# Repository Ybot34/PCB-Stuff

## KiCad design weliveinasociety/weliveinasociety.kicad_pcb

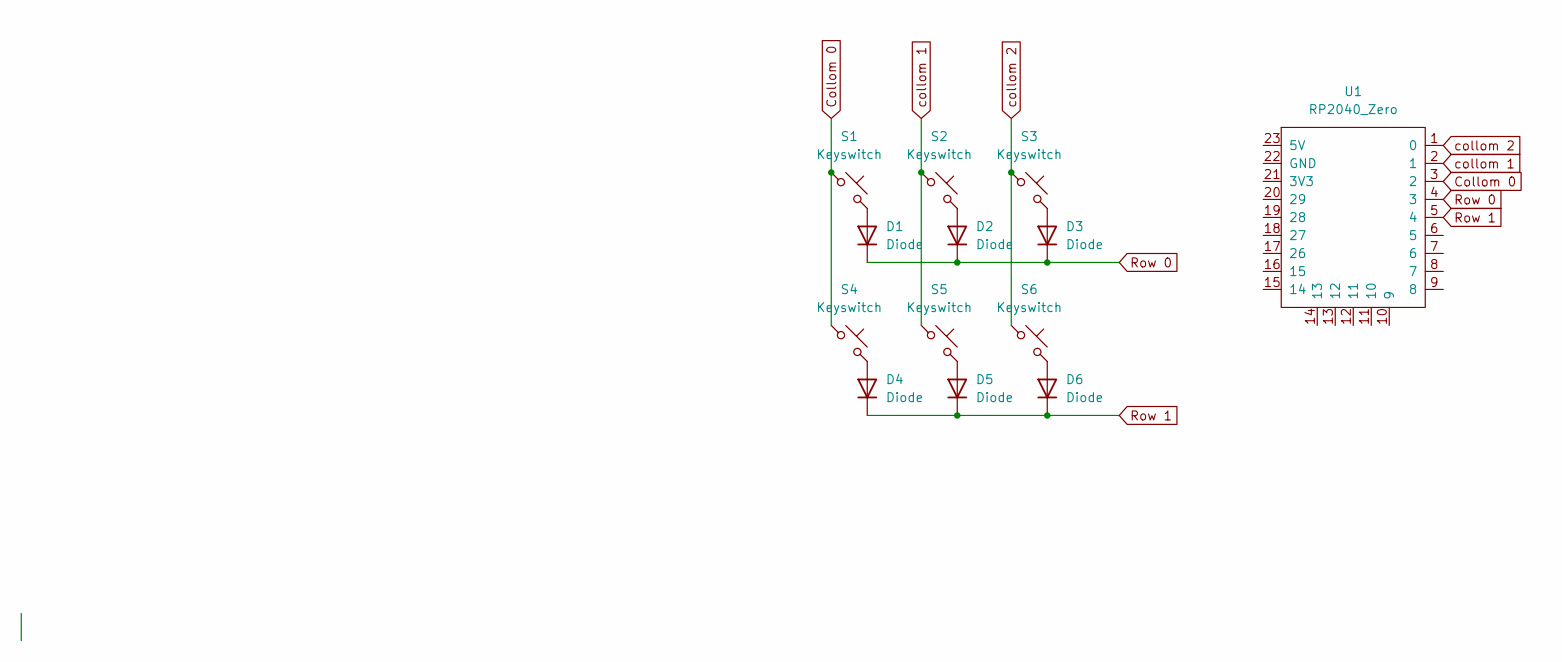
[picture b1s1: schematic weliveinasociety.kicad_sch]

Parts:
D1, D2, D3, D4, D5, D6: Diode; Diode_DO-35
S1, S2, S3, S4, S5, S6: Keyswitch; MX_PCB_1.00u
U1: RP2040_Zero

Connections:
Collom 0: S1.1, S4.1, U1.3 (2)
unnamed: D1.2 (A), S1.2
unnamed: D2.2 (A), S2.2
unnamed: D3.2 (A), S3.2
unnamed: D4.2 (A), S4.2
unnamed: D5.2 (A), S5.2
unnamed: D6.2 (A), S6.2
Row 0: D1.1 (K), D2.1 (K), D3.1 (K), U1.4 (3)
Row 1: D4.1 (K), D5.1 (K), D6.1 (K), U1.5 (4)
collom 1: S2.1, S5.1, U1.2 (1)
collom 2: S3.1, S6.1, U1.1 (0)

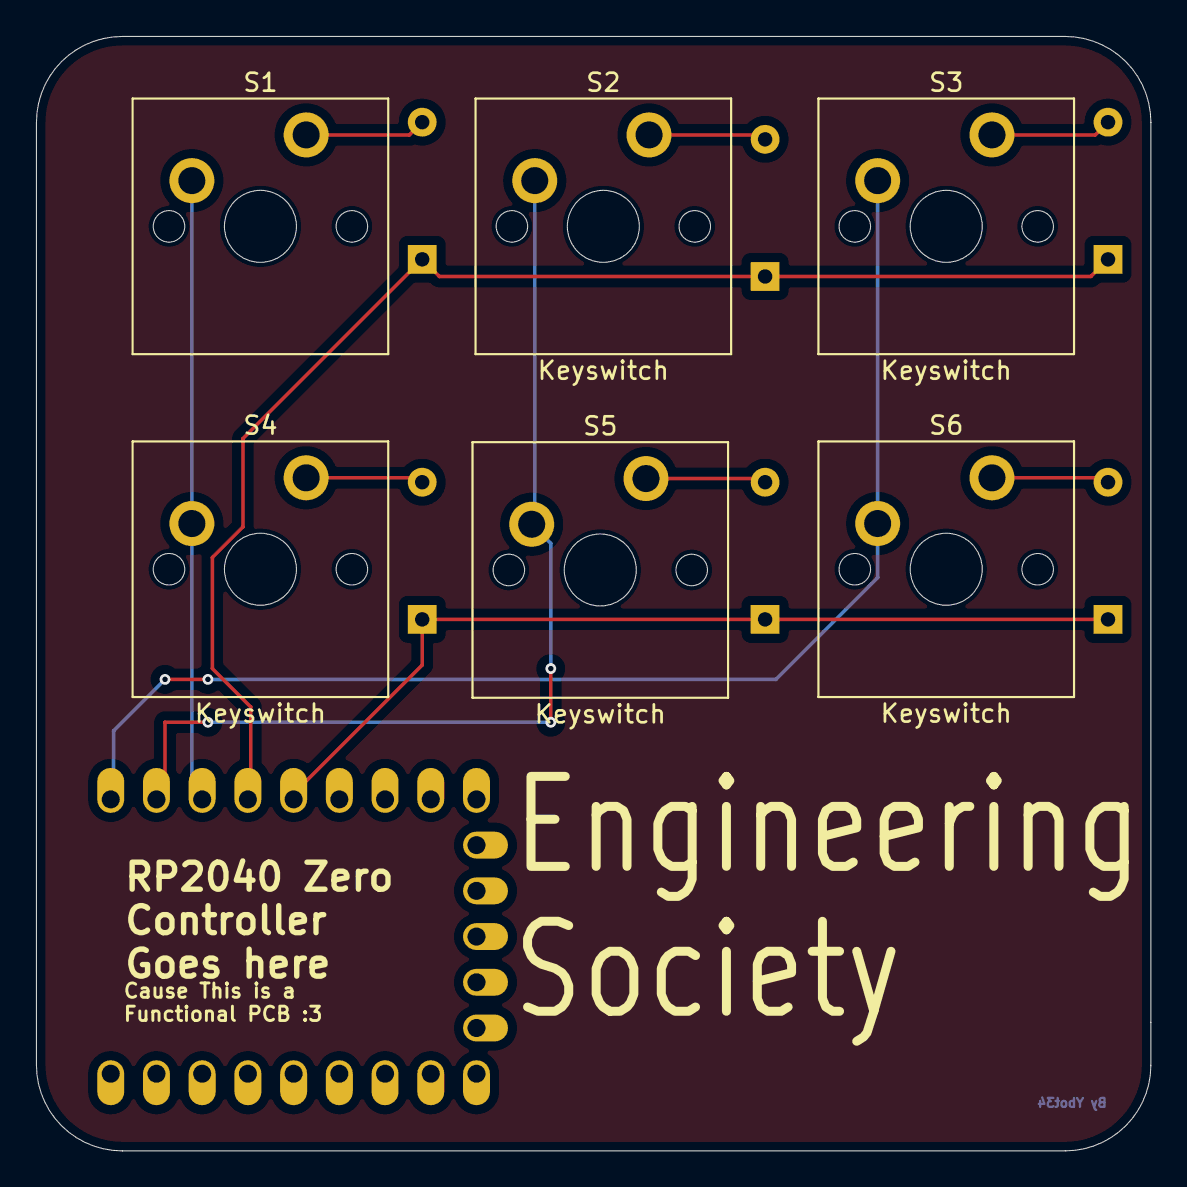
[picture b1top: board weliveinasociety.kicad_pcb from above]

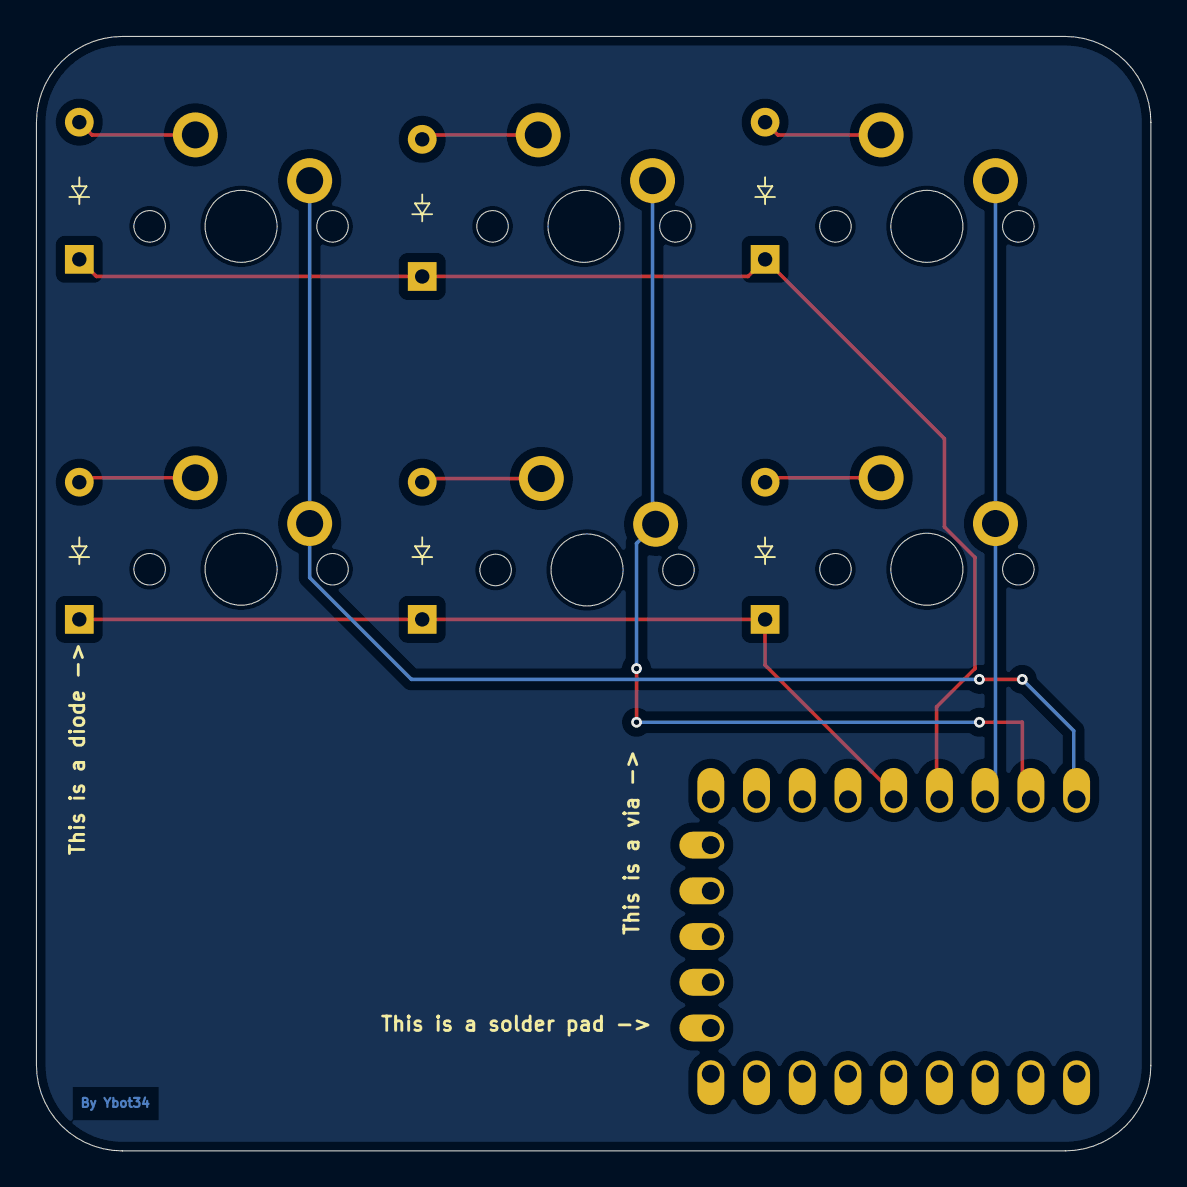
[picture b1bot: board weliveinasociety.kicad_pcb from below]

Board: 2 copper layers, 61.9 x 61.9 mm, 13 parts (6 on the bottom side), 11 nets.

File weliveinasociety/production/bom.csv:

Designator,Footprint,Quantity,Value,LCSC Part #
"D1, D2, D3, D4, D5, D6",Diode_DO-35,6,Diode,
"S1, S2, S3, S4, S5, S6",MX_PCB_1.00u,6,Keyswitch,
U1,RP2040_Zero,1,RP2040_Zero,

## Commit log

2025-08-21 Engineering Society PCB project files and images
    Gerber files in production folder
